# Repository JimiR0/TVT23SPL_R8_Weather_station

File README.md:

# TVT23SPL_R8_Weather_station
# Electronics Application Project

The electronics application project is part of the second-year studies in the Bachelor’s Degree in Information and Communication Technology. It serves as the final project for the second year and has been designed to challenge students and their skills by requiring them to build a device of their own choosing, which includes an analog interface and a microcontroller.
________________________________________
## Project Architecture

________________________________________
## Project Goal
The main goals of the project were:

•	To design and build a functional PCB

•	To build a functional and portable weather station around the PCB, equipped with sensors for wind speed, humidity, air pressure, and temperature

•	To transmit the sensor values via Bluetooth to a computer, and via wires to an OLED display

•	To integrate the weather station into a hat
________________________________________
## Practical Experience

•	Designing and building a PCB

•	Soldering small components onto the PCB

•	Device-oriented design

•	Deeper understanding of Bluetooth Low Energy
________________________________________
## Project Implementation in Phases

Phase 1: Coming up with the project idea and planning its implementation

Phase 2: Ordering the components and starting to write code

Phase 3: Designing and ordering the PCB

Phase 4: Soldering the components onto the PCB and testing functionality

Phase 5: Finalizing the code to working condition

Phase 6: Assembling the project and testing it for presentation
________________________________________
## Devices and Technology Used

Here you can find the components, applications and devices that helped with the project:

•	KiCad

•	Arduino IDE

•	ESP32 Wroom 1

•	OLED display

•	BME280 sensor

•	TCST1103 Photo Interrupter

(KUVA 1. ESP32 Devkit)

(KUVA 2. OLED-näyttö)

(KUVA 3. BME280 sensori)

(KUVA 4. TCST1103 Optohaarukka)

________________________________________
## Learning Experiences and Challenges

During the project, we gained extensive experience in device-oriented design and programming. Especially the circuit design and implementation provided both learning opportunities and challenges. The most difficult part turned out to be getting the entire system to work together.
Challenges included:
•	Designing the PCB to be just right for our use
•	Getting the optical fork (opto-interrupter) to work with the ESP32
•	Displaying data correctly on the OLED display
•	Fitting all project components into a hat
________________________________________
## Hardware Links

ESP32 Devkit
________________________________________
## Summary

The electronics application project was a challenging experience in terms of skills and learning, and it was the most demanding part of the academic year. However, it was extremely educational and valuable for our future careers. The goal of our project was to build a functional, head-worn weather station that displays wind speed, humidity, and temperature in real time to the user. We believe we succeeded in the project, as we met the goals we had set for ourselves, and the project was a success.

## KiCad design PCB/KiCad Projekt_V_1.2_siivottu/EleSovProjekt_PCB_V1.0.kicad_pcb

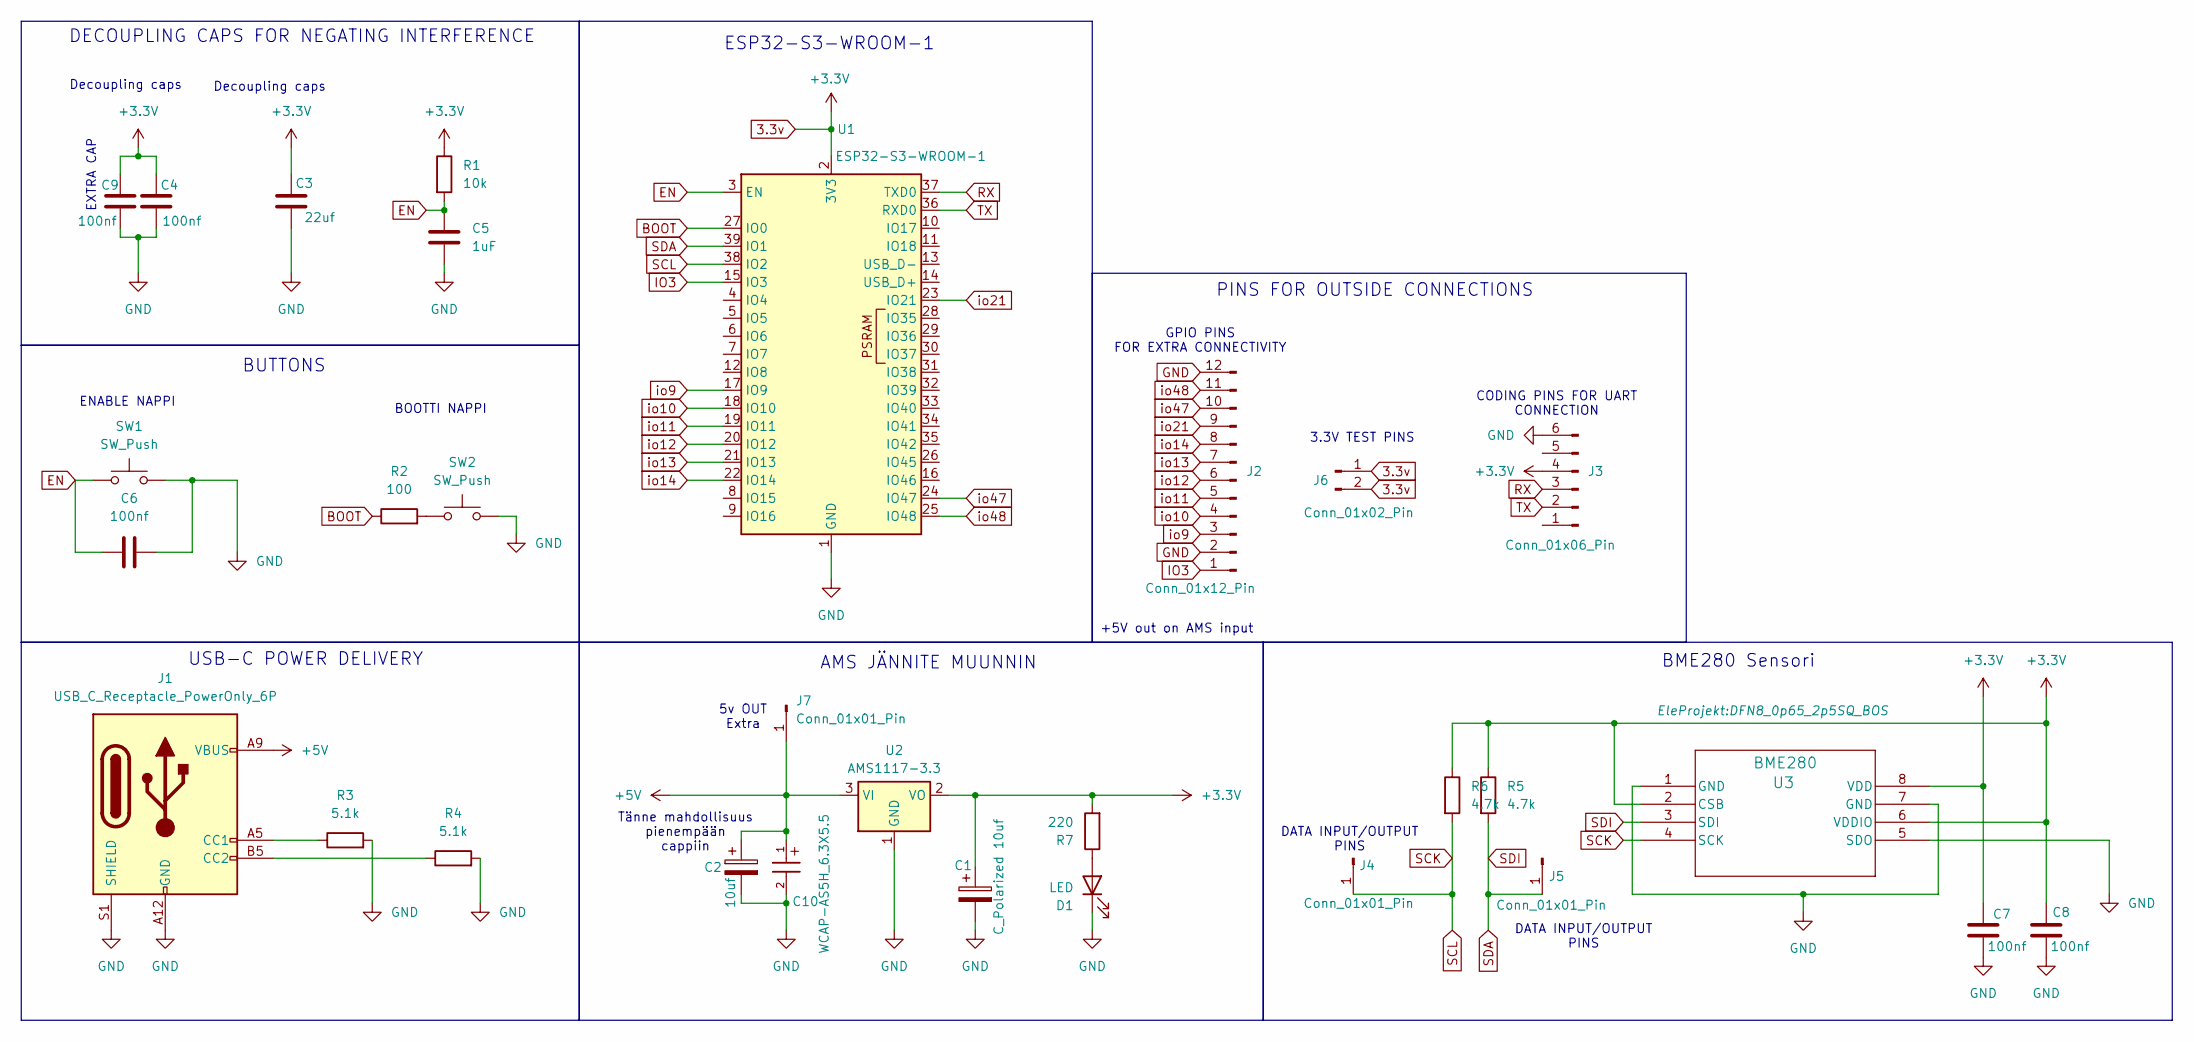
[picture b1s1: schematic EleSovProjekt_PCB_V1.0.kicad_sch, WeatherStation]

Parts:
C1: C_Polarized 10uf; C_0805_2012Metric_Pad1.18x1.45mm_HandSolder
C2: 10uf; C_0805_2012Metric_Pad1.18x1.45mm_HandSolder
C3: 22uf; CP_Radial_D5.0mm_P2.00mm
C4, C6, C7, C8, C9: 100nf; C_0805_2012Metric_Pad1.18x1.45mm_HandSolder
C5: 1uF; C_0805_2012Metric_Pad1.18x1.45mm_HandSolder
C10: WCAP-AS5H_6.3X5.5; WCAP-AS5H_6.3X5.5_DXL_
D1: LED; LED_D2.0mm_W4.8mm_H2.5mm_FlatTop
J1: USB_C_Receptacle_PowerOnly_6P; USB_C_Receptacle_GCT_USB4125-xx-x-0190_6P_TopMnt_Horizontal
J2: Conn_01x12_Pin; PinHeader_1x12_P2.54mm_Vertical
J3: Conn_01x06_Pin; PinHeader_1x06_P2.54mm_Horizontal
J4, J5, J7: Conn_01x01_Pin; PinHeader_1x01_P2.54mm_Vertical
J6: Conn_01x02_Pin; PinHeader_1x02_P2.54mm_Vertical
R1: 10k; R_0805_2012Metric_Pad1.20x1.40mm_HandSolder
R2: 100; R_0805_2012Metric_Pad1.20x1.40mm_HandSolder
R3, R4: 5.1k; R_0603_1608Metric_Pad0.98x0.95mm_HandSolder
R5, R6: 4.7k; R_1206_3216Metric_Pad1.30x1.75mm_HandSolder
R7: 220; R_1206_3216Metric_Pad1.30x1.75mm_HandSolder
SW1, SW2: SW_Push; SW_MEC_5GTH9
U1: ESP32-S3-WROOM-1
U2: AMS1117-3.3; SOT-223-3_TabPin2
U3: BME280; DFN8_0p65_2p5SQ_BOS

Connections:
3.3v: C1.1, C3.1, C4.1, C7.1, C8.1, C9.1, J3.4, J6.1, J6.2, R1.1, R5.1, R6.1, R7.2, SW1.1, SW2.1, U1.2 (3V3), U2.2 (VO), U3.2 (CSB), U3.6 (VDDIO), U3.8 (VDD)
+5V: C2.1, C10.1, J1.A9 (VBUS), J1.B9 (VBUS), J7.1, U2.3 (VI)
BOOT: R2.1, U1.27 (IO0)
EN: C5.1, C6.1, R1.2, SW1.1, U1.3 (EN)
GND: C1.2, C2.2, C3.2, C4.2, C5.2, C6.2, C7.2, C8.2, C9.2, C10.2, D1.1 (K), J1.A12 (GND), J1.B12 (GND), J1.S1 (SHIELD), J2.2, J2.12, J3.6, R3.2, R4.2, SW1.2, SW2.2, U1.1 (GND), U1.40 (GND), U1.41 (GND), U2.1 (GND), U3.1 (GND), U3.5 (SDO), U3.7 (GND)
IO3: J2.1, U1.15 (IO3)
unnamed: D1.2 (A), R7.1
unnamed: J1.A5 (CC1), R3.1
unnamed: J1.B5 (CC2), R4.1
unnamed: R2.2, SW2.1
RX: J3.3, U1.37 (TXD0)
SCK: J4.1, R6.2, U1.38 (IO2), U3.4 (SCK)
SDA: J5.1, R5.2, U1.39 (IO1), U3.3 (SDI)
TX: J3.2, U1.36 (RXD0)
io9: J2.3, U1.17 (IO9)
io10: J2.4, U1.18 (IO10)
io11: J2.5, U1.19 (IO11)
io12: J2.6, U1.20 (IO12)
io13: J2.7, U1.21 (IO13)
io14: J2.8, U1.22 (IO14)
io21: J2.9, U1.23 (IO21)
io47: J2.10, U1.24 (IO47)
io48: J2.11, U1.25 (IO48)

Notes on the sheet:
BME280 Sensori
Tänne mahdollisuus pienempään cappiin
DATA INPUT/OUTPUT PINS
EXTRA CAP
Decoupling caps
5v OUT Extra
GPIO PINS FOR EXTRA CONNECTIVITY
USB-C POWER DELIVERY
3.3V TEST PINS
DECOUPLING CAPS FOR NEGATING INTERFERENCE
ENABLE NAPPI
+5V out on AMS input
PINS FOR OUTSIDE CONNECTIONS
BUTTONS
ESP32-S3-WROOM-1
BOOTTI NAPPI
AMS JÄNNITE MUUNNIN
CODING PINS FOR UART CONNECTION

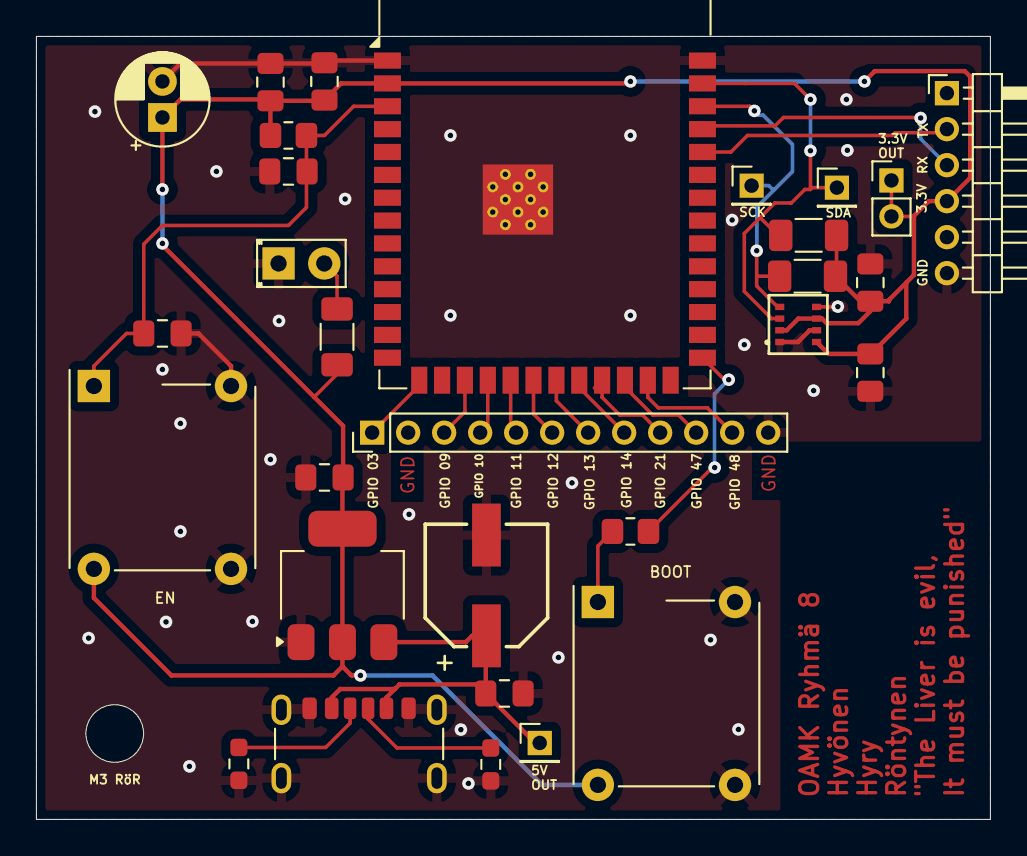
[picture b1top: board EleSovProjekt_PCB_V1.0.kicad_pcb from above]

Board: 2 copper layers, 53.0 x 43.5 mm, 30 parts (0 on the bottom side), 23 nets.

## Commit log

2025-04-08 PCB,Code
    first iterations of code and older and final version of PCB
2025-04-08 Pictures
    Pictures of PCB,Schema and overall connectivity
2025-04-25 Add files via upload
    Sää+RPM koodi
2025-04-28 Add files via upload
    Now with m/s
